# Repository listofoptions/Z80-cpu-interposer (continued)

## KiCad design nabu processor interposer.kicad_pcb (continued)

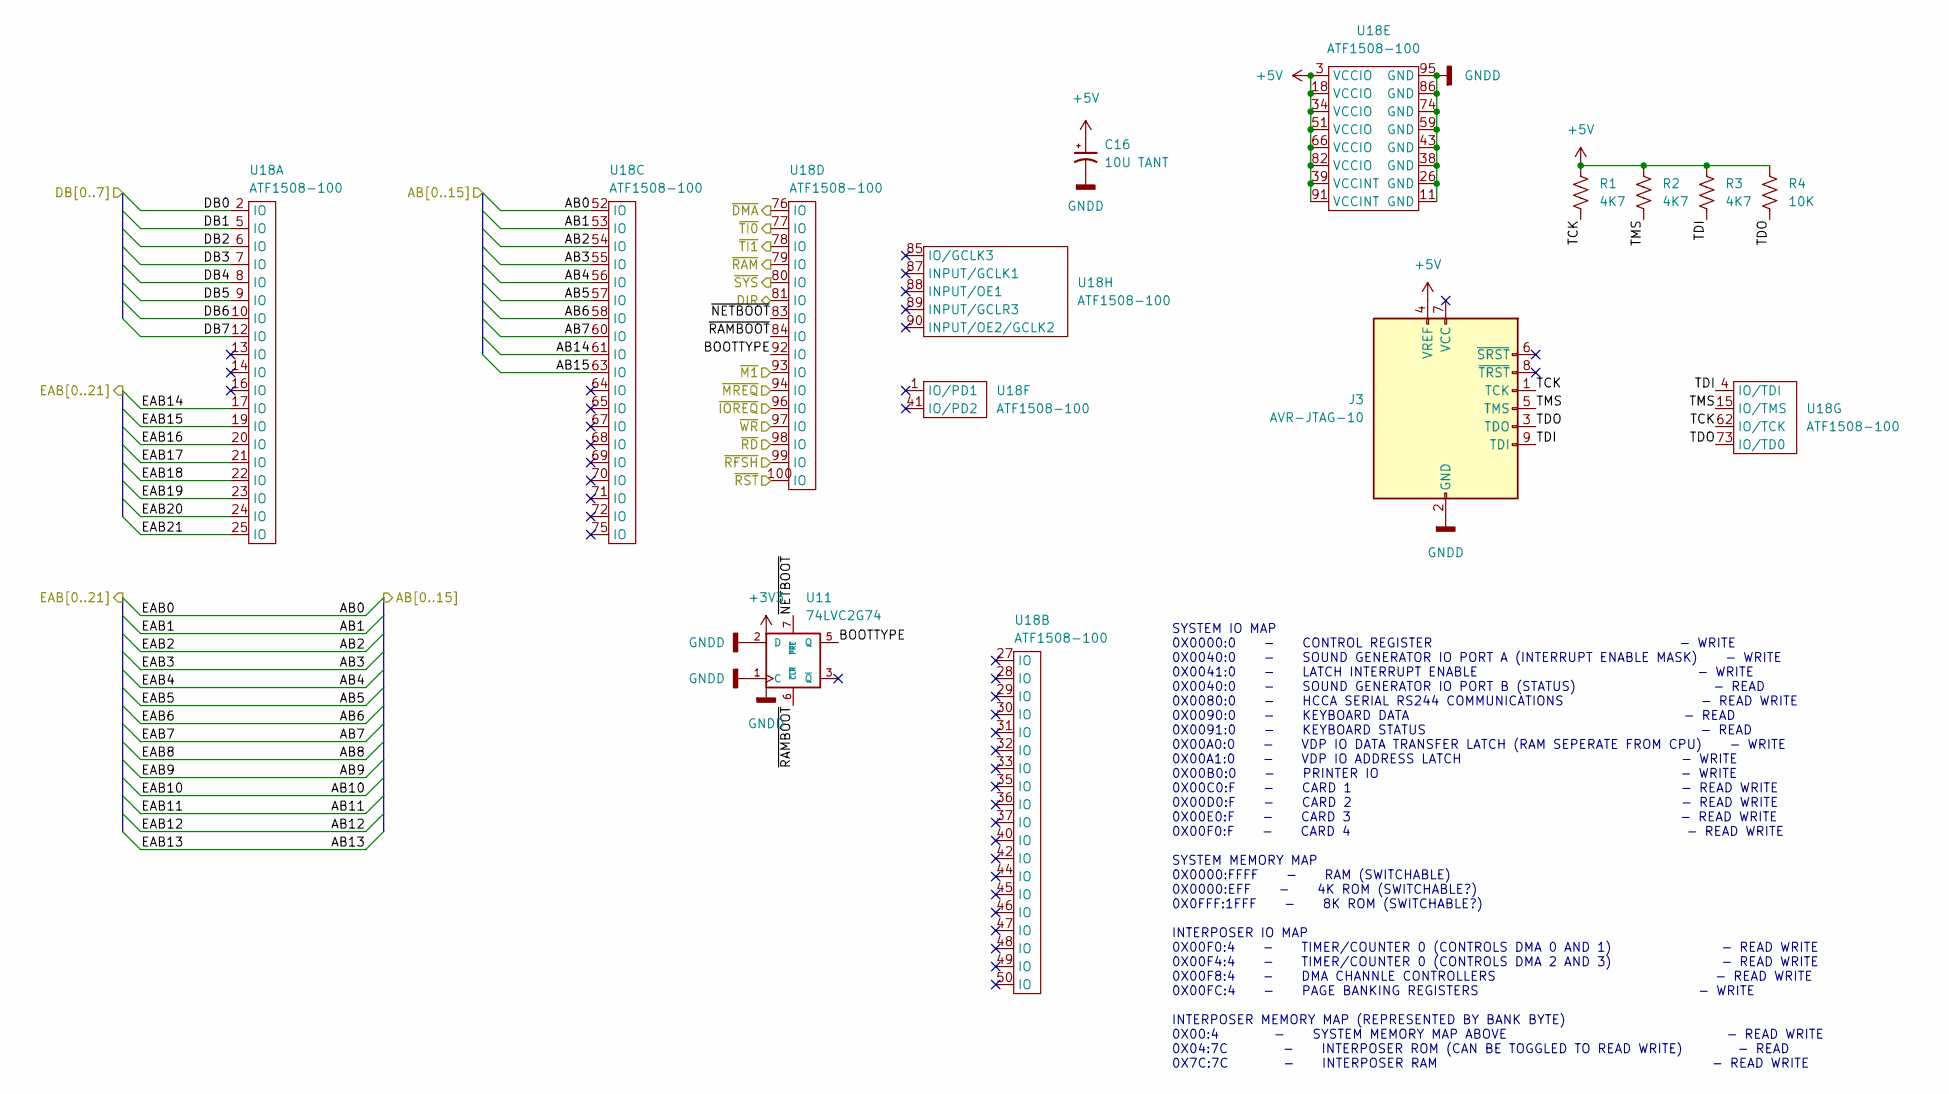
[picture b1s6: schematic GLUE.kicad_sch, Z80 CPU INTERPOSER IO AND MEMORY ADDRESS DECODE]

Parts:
C16: 10U TANT; CP_EIA-3528-15_AVX-H
J3: AVR-JTAG-10; IDC-Header_2x05_P2.54mm_Horizontal
R1, R2, R3: 4K7; R_0603_1608Metric
R4: 10K; R_0603_1608Metric
U11: 74LVC2G74; SOT-363_SC-70-6
U18: ATF1508-100; TQFP-144_16x16mm_P0.4mm

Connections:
+5V: C16.1, J3.4 (VREF), R1.1, R2.1, R3.1, R4.1, U18.3 (VCCIO), U18.18 (VCCIO), U18.34 (VCCIO), U18.39 (VCCINT), U18.51 (VCCIO), U18.66 (VCCIO), U18.82 (VCCIO), U18.91 (VCCINT); also elsewhere on the board
/BRAINS/AB0: U18.52 (IO); also elsewhere on the board
/BRAINS/AB1: U18.53 (IO); also elsewhere on the board
/BRAINS/AB2: U18.54 (IO); also elsewhere on the board
/BRAINS/AB3: U18.55 (IO); also elsewhere on the board
/BRAINS/AB4: U18.56 (IO); also elsewhere on the board
/BRAINS/AB5: U18.57 (IO); also elsewhere on the board
/BRAINS/AB6: U18.58 (IO); also elsewhere on the board
/BRAINS/AB7: U18.60 (IO); also elsewhere on the board
/BRAINS/AB14: U18.61 (IO); also elsewhere on the board
/BRAINS/AB15: U18.63 (IO); also elsewhere on the board
/BRAINS/DB0: U18.2 (IO); also elsewhere on the board
/BRAINS/DB1: U18.5 (IO); also elsewhere on the board
/BRAINS/DB2: U18.6 (IO); also elsewhere on the board
/BRAINS/DB3: U18.7 (IO); also elsewhere on the board
/BRAINS/DB4: U18.8 (IO); also elsewhere on the board
/BRAINS/DB5: U18.9 (IO); also elsewhere on the board
/BRAINS/DB6: U18.10 (IO); also elsewhere on the board
/BRAINS/DB7: U18.12 (IO); also elsewhere on the board
/BRAINS/DIR: U18.81 (IO); also elsewhere on the board
/BRAINS/~IOREQ: U18.96 (IO); also elsewhere on the board
/BRAINS/~M1: U18.93 (IO); also elsewhere on the board
/BRAINS/~MREQ: U18.94 (IO); also elsewhere on the board
/BRAINS/~RD: U18.98 (IO); also elsewhere on the board
/BRAINS/~RFSH: U18.99 (IO); also elsewhere on the board
/BRAINS/~RST: U18.100 (IO); also elsewhere on the board
/BRAINS/~SYS: U18.80 (IO); also elsewhere on the board
/BRAINS/~WR: U18.97 (IO); also elsewhere on the board
/DMA/~DMA: U18.76 (IO); also elsewhere on the board
/GLUE/BOOTTYPE: U11.5 (Q), U18.92 (IO)
/GLUE/EAB14: U18.17 (IO); also elsewhere on the board
/GLUE/EAB15: U18.19 (IO); also elsewhere on the board
/GLUE/EAB16: U18.20 (IO); also elsewhere on the board
/GLUE/EAB17: U18.21 (IO); also elsewhere on the board
/GLUE/EAB18: U18.22 (IO); also elsewhere on the board
/GLUE/EAB19: U18.23 (IO); also elsewhere on the board
/GLUE/EAB20: U18.24 (IO); also elsewhere on the board
/GLUE/EAB21: U18.25 (IO); also elsewhere on the board
/GLUE/TCK: J3.1 (TCK), R1.2, U18.62 (IO/TCK)
/GLUE/TDI: J3.9 (TDI), R3.2, U18.4 (IO/TDI)
/GLUE/TDO: J3.3 (TDO), R4.2, U18.73 (IO/TD0)
/GLUE/TMS: J3.5 (TMS), R2.2, U18.15 (IO/TMS)
/GLUE/~NETBOOT: U11.7 (~PRE), U18.83 (IO)
/GLUE/~RAMBOOT: U11.6 (~CLR), U18.84 (IO)
/GLUE/~RAM: U18.79 (IO)
/GLUE/~TI0: U18.77 (IO); also elsewhere on the board
/GLUE/~TI1: U18.78 (IO); also elsewhere on the board
GND: C16.2, J3.2 (GND), J3.10 (GND), U11.1 (C), U11.2 (D), U11.4 (GND), U18.11 (GND), U18.26 (GND), U18.38 (GND), U18.43 (GND), U18.59 (GND), U18.74 (GND), U18.86 (GND), U18.95 (GND); also elsewhere on the board

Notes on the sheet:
SYSTEM IO MAP 0X0000:0 - CONTROL REGISTER - WRITE 0X0040:0 - SOUND GENERATOR IO PORT A (INTERRUPT ENABLE MASK) - WRITE 0X0041:0 - LATCH INTERRUPT ENABLE - WRITE 0X0040:0 - SOUND GENERATOR IO PORT B (STATUS) - READ 0X0080:0 - HCCA SERIAL RS244 COMMUNICATIONS - READ WRITE 0X0090:0 - KEYBOARD DATA - R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

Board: 4 copper layers, 53 parts (26 on the bottom side), 139 nets, no tracks yet.

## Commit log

2022-10-25 added more notes and documentation
    todo:
    - timing analysis to make sure everything fits in 250nS + hold time/prep time
    - logic analysis to ensure correct functionality (am gonna make dumb mistakes!)
    - board layout
    - physical testing!
2022-10-25 fixed non obvious bug in mapper circuit reset logic, would be possible to have the latches both clocked and reset at the same time!, now only resets when in reset, and only clocks when not in reset
2022-10-25 changed bus names to avoid possible conflicts, fixed unnamed busses.
2022-10-25 added decoupling capacitors, perhaps too many? idk better more than less!
2022-10-26 stuff
2022-10-26 distrustful of timing on reset of mapping registers
2022-10-26 duh obvious optimization
2022-10-26 more obvious optimizations
2022-10-26 some clean up and simplification, as well as some renaming
2022-12-03 begin integration of logic into atf1508
2022-12-03 added ATF150x part (specifically the 1508) vhdl file contains the (hopeful) implementition of the mapper
2022-12-05 updated 84c10 pinout, apparently never checked for validity.... further simplification of dma and timer system (removed mode 2 interrupt structure, and interrupts in general) cleaned up vhdl code for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
2022-12-05 removed binary files, cleaned cpld code; need testbench for cpld
2022-12-05 forgot to actually add the previous fixes to kicad
2022-12-07 fixed logic errors (me being dumb forgetting associativity of ops, and fixed write only system databus on interposer
2022-12-08 Added R5: a pull-up resistor for the /BUSREQ pin
2022-12-08 Removed project local settings (.kicad_prl), these are usually not stored with revision control.
2022-12-16 fixed extra nand_reduce (issue #8)
    set default data bus driver direction to 'high' ie to read from the databus
    only, we should be to get away with this since sys_dir should be disabling
    the buffer regaurdless if both rd_n and wr_n are in the inactive states.
    (issue #6)
    fixed a silly mixup in pin driver direction (issue #5)
    pin names changed per request (issue #7) to reflect active low, also when
2022-12-16 see previous commit, wrote thing before i added woops
2022-12-16 simplified the vhdl code for the mapper by removing some of the more complex initilization logic used: flags was initially intended to be used for reset logic but was determined to be un-needed if we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
    control_regs was going to shadow the main system control
    register, but only contain the bits not used by the system.
    removed for now since im not sure that those bits arent
    written anyway by software. the eventual intention is to
    allow bits 7 and 8 to determine if mapping is wanted at all
    and to boot from interposer rom instead of network (which may
2022-12-16 forgot to clean up built binaries
2022-12-26 final hardware revision
    final update to the hardware:
    - removed flash
    - added battery backup switch-over
    - increased ram to 4MB
    - added ramboot/netboot option by using reads to write-only ports to trigger/toggle
    - fixed a logic bug i should have caught in writes to the mapper registers (using bits 14&15 instead of 1&0)
